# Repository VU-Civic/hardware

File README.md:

# CivicAlert Hardware Design Repository

This repository contains hardware design files for the CivicAlert sensor device. The design was created
using [KiCad](https://www.kicad.org/download) and requires v9.0.0 or later to open and edit.

The CivicAlert gunshot sensor is a self-contained PCB which utilizes four audio channels, a digital
compass and IMU, GNSS satellite data, and a state-of-the-art AI-based classification model to detect
gunshots in its vicinity. Relevant event information and evidential audio clips can be transferred to
a cloud server for futher processing using a dedicated cellular-based Internet of Things (IoT) network.

## Getting Started

1. Clone this repo on your local machine
2. Download and install [KiCad](https://www.kicad.org/download)
3. Open KiCad
4. Click `File->Open Project`
5. Select `hw.kicad_pro` from the repo root directory

You will be presented with a listing of available KiCad tools for this project. The two most relevant are
the "Schematic Editor" and the "PCB Editor". The Schematic Editor allows you to view and manipulate the
logical connections between hardware components and power networks, while the "PCB Editor" allows you to
view the actual design of the board and layout of the components as they will be placed during
manufacturing and assembly.

The schematic symbols and footprints for all parts and components used in this design have been stored
within the repo itself and should automatically be picked up by KiCad when you open the project. If you
would like to add new parts or alter existing ones, you may use the "Symbol Editor" or "Footprint
Editor" tool, and ensure that any new parts are stored in either `part_symbols/` or `part_footprints/`
so that new parts will be visible and available to others in the future.

Additionally, 3D CAD models for all parts can be found in `part_3d_cads/`, which will be used by KiCad
to generate a 3D rendering of the final assembled board. Finally, all datasheets, application notes,
and relevant part-specific documentation can be in the `datasheets/` folder.

## Revisions

### Revision A
*Release Date: 03-13-2025*

Original prototype version of the hardware. Expected usage includes:

* 4 audio channels to allow computation of 3D angles of arrival
* Digital compass + IMU to align angles of arrival with a global coordinate system
* Multi-constellation GNSS receiver to ensure accurate timestamping in difficult environments
* Micro-SIM card to provide direct connectivity to Thingstream for cellular data offloading
* Event detection and angle of arrival calculations performed on primary MCU
* Event classification and validation performed using AI models on external Raspberry Pi
* Data communication between primary MCU and Raspberry Pi uses USB over internal connector
* Data communication between primary MCU and external debugging machine (PC) uses USB-C connector
* Internal switch automatically routes primary MCU output to correct USB interface depending on the
  presence or absence of a connected Raspberry Pi Compute Module
* Entire board (including Raspberry Pi) is powered from a 5V USB-C cable
* Firmware flashing requires an open-ended card edge connector from
  [Kyocera AVX](https://www.digikey.com/en/products/detail/kyocera-avx/009159010061911/11307835)
  and an STLink-V3MINIE programmer from
  [STMicroelectronics](https://www.digikey.com/en/products/detail/stmicroelectronics/STLINK-V3MINIE/16284301)

Major functionality and components are shown below:

### Revision B
*Release Date: 08-01-2025*

Updated to support edge-based AI and remove the need for an external Raspberry Pi Compute Module:

TODO: Board Designs

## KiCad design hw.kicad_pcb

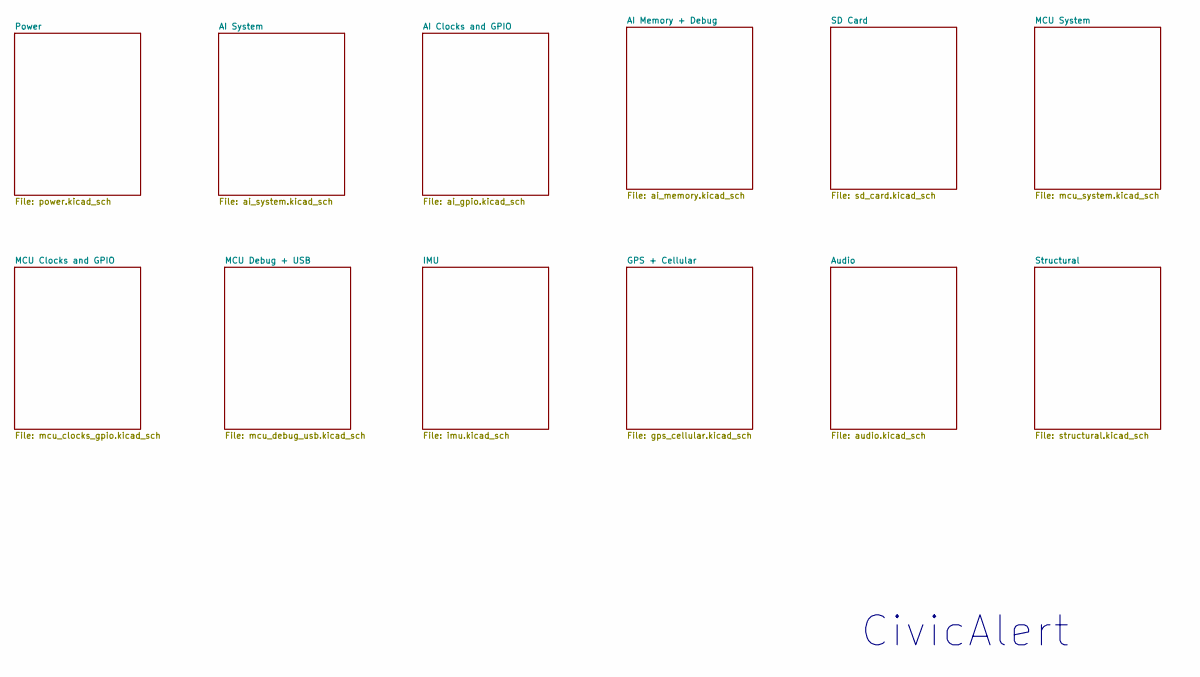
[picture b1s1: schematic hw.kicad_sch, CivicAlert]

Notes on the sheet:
CivicAlert

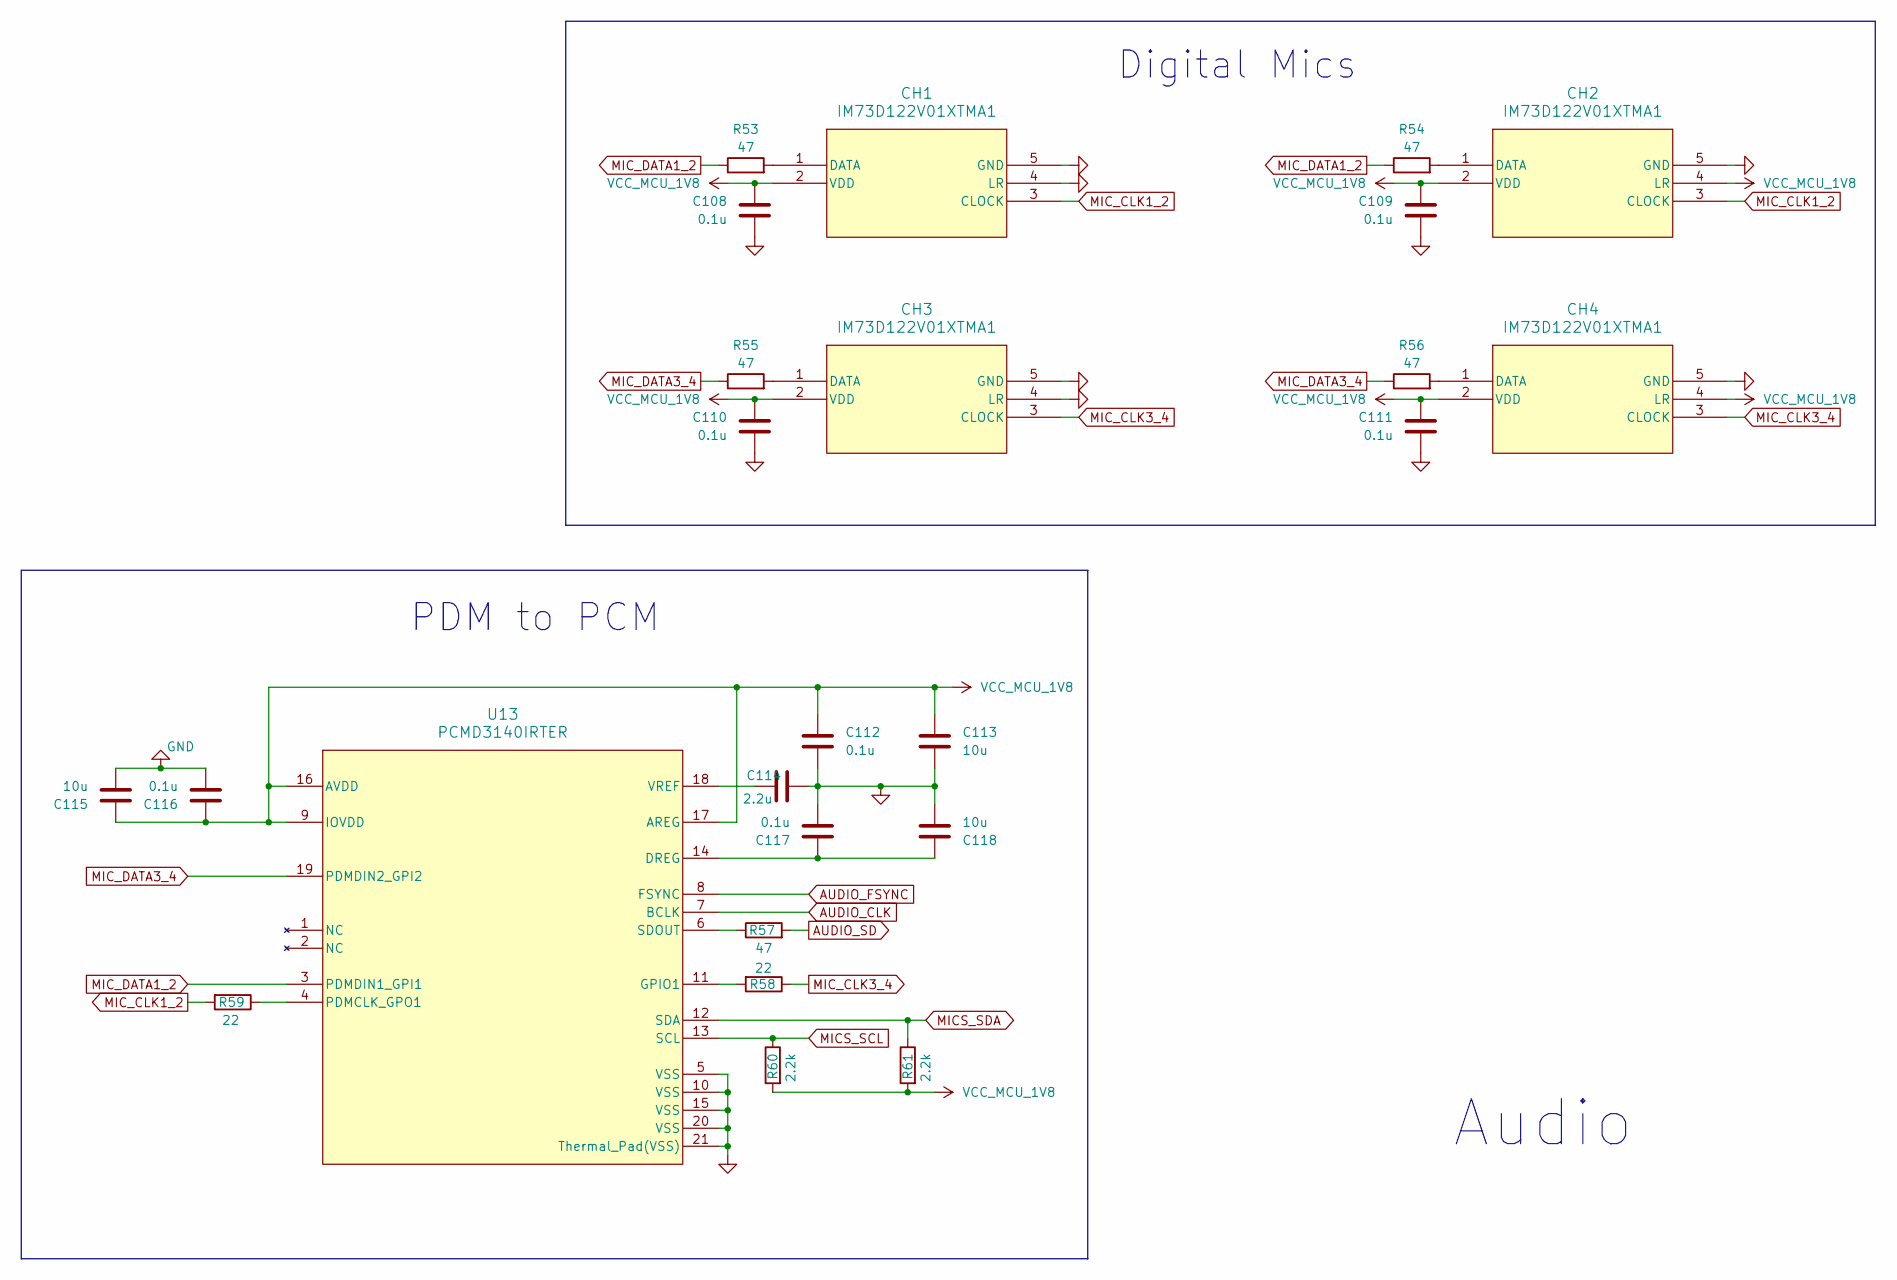
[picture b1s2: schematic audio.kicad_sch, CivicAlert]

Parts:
C108, C109, C110, C111, C112, C116, C117: 0.1u; C_0402_1005Metric; MPN GRM155R71C104KA88J
C113, C115, C118: 10u; C_0603_1608Metric; MPN GRM188Z71A106KA73D
C114: 2.2u; C_0402_1005Metric; MPN GRT155C71A225KE13D
CH1, CH2, CH3, CH4: IM73D122V01XTMA1; MPN IM73D122V01XTMA1
R53, R54, R55, R56, R57: 47; R_0402_1005Metric
R58, R59: 22; R_0402_1005Metric
R60, R61: 2.2k; R_0402_1005Metric
U13: PCMD3140IRTER; MPN PCMD3140IRTER

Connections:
AUDIO_CLK: U13.7 (BCLK); also elsewhere on the board
AUDIO_FSYNC: U13.8 (FSYNC); also elsewhere on the board
AUDIO_SD: R57.2; also elsewhere on the board
GND: C108.2, C109.2, C110.2, C111.2, C112.2, C113.2, C114.2, C115.2, C116.2, C117.2, C118.2, CH1.4 (LR), CH1.5 (GND), CH2.5 (GND), CH3.4 (LR), CH3.5 (GND), CH4.5 (GND), U13.5 (VSS), U13.10 (VSS), U13.15 (VSS), U13.20 (VSS), U13.21 (Thermal_Pad(VSS)); also elsewhere on the board
MICS_SCL: R60.1, U13.13 (SCL); also elsewhere on the board
MICS_SDA: R61.1, U13.12 (SDA); also elsewhere on the board
MIC_CLK1_2: CH1.3 (CLOCK), CH2.3 (CLOCK), R59.2
MIC_CLK3_4: CH3.3 (CLOCK), CH4.3 (CLOCK), R58.1
MIC_DATA1_2: R53.1, R54.1, U13.3 (PDMDIN1_GPI1)
MIC_DATA3_4: R55.1, R56.1, U13.19 (PDMDIN2_GPI2)
unnamed: CH1.1 (DATA), R53.2
unnamed: CH2.1 (DATA), R54.2
unnamed: CH3.1 (DATA), R55.2
unnamed: CH4.1 (DATA), R56.2
unnamed: C117.1, C118.1, U13.14 (DREG)
unnamed: R58.2, U13.11 (GPIO1)
unnamed: R59.1, U13.4 (PDMCLK_GPO1)
unnamed: R57.1, U13.6 (SDOUT)
unnamed: C114.1, U13.18 (VREF)
VCC_MCU_1V8: C108.1, C109.1, C110.1, C111.1, C112.1, C113.1, C115.1, C116.1, CH1.2 (VDD), CH2.2 (VDD), CH2.4 (LR), CH3.2 (VDD), CH4.2 (VDD), CH4.4 (LR), R60.2, R61.2, U13.9 (IOVDD), U13.16 (AVDD), U13.17 (AREG); also elsewhere on the board

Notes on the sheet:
Digital Mics
PDM to PCM
Audio

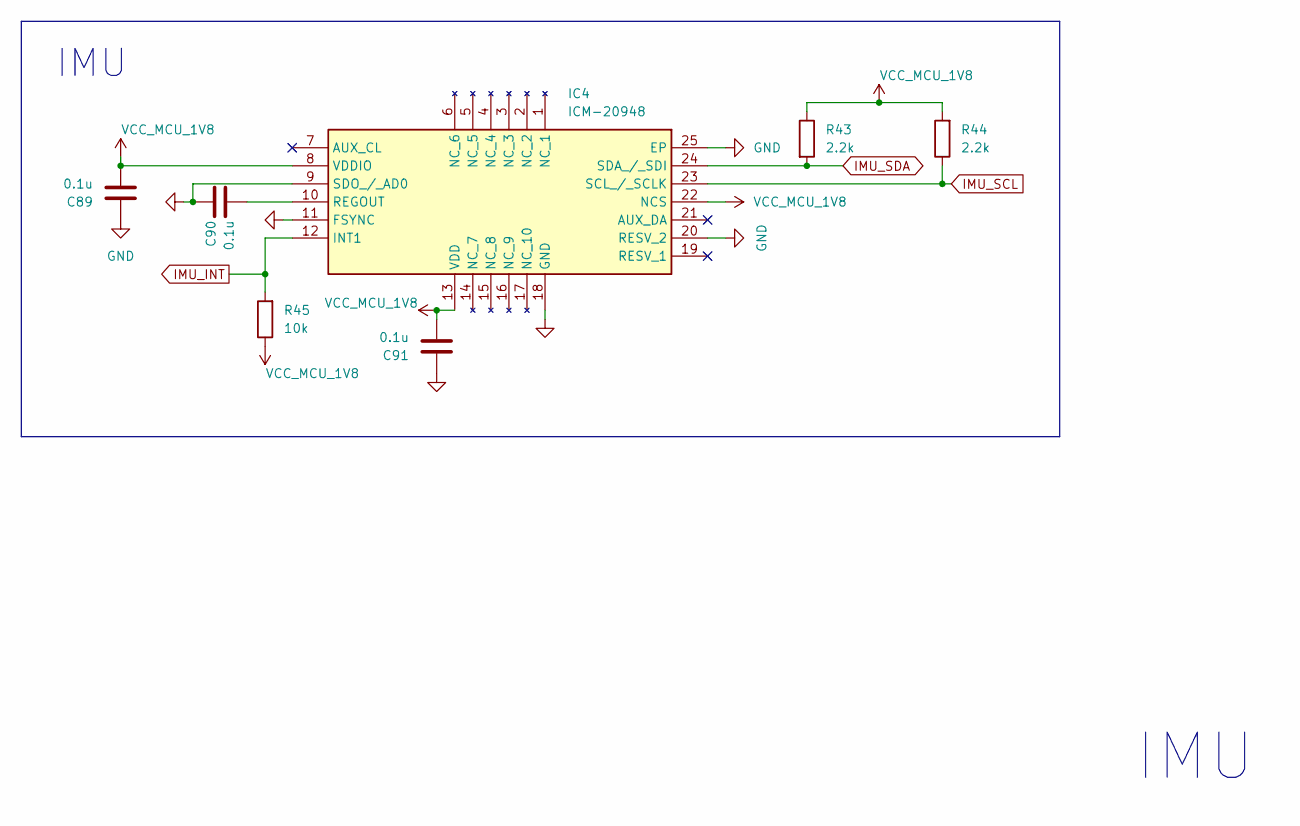
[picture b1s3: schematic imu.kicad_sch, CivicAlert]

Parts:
C89, C90, C91: 0.1u; C_0402_1005Metric; MPN GRM155R71C104KA88J
IC4: ICM-20948; MPN ICM-20948
R43, R44: 2.2k; R_0402_1005Metric
R45: 10k; R_0402_1005Metric

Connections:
GND: C89.1, C90.1, C91.1, IC4.9 (SDO_/_AD0), IC4.11 (FSYNC), IC4.18 (GND), IC4.20 (RESV_2), IC4.25 (EP); also elsewhere on the board
IMU_INT: IC4.12 (INT1), R45.2; also elsewhere on the board
IMU_SCL: IC4.23 (SCL_/_SCLK), R44.1; also elsewhere on the board
IMU_SDA: IC4.24 (SDA_/_SDI), R43.2; also elsewhere on the board
unnamed: C90.2, IC4.10 (REGOUT)
VCC_MCU_1V8: C89.2, C91.2, IC4.8 (VDDIO), IC4.13 (VDD), IC4.22 (NCS), R43.1, R44.2, R45.1; also elsewhere on the board

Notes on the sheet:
IMU

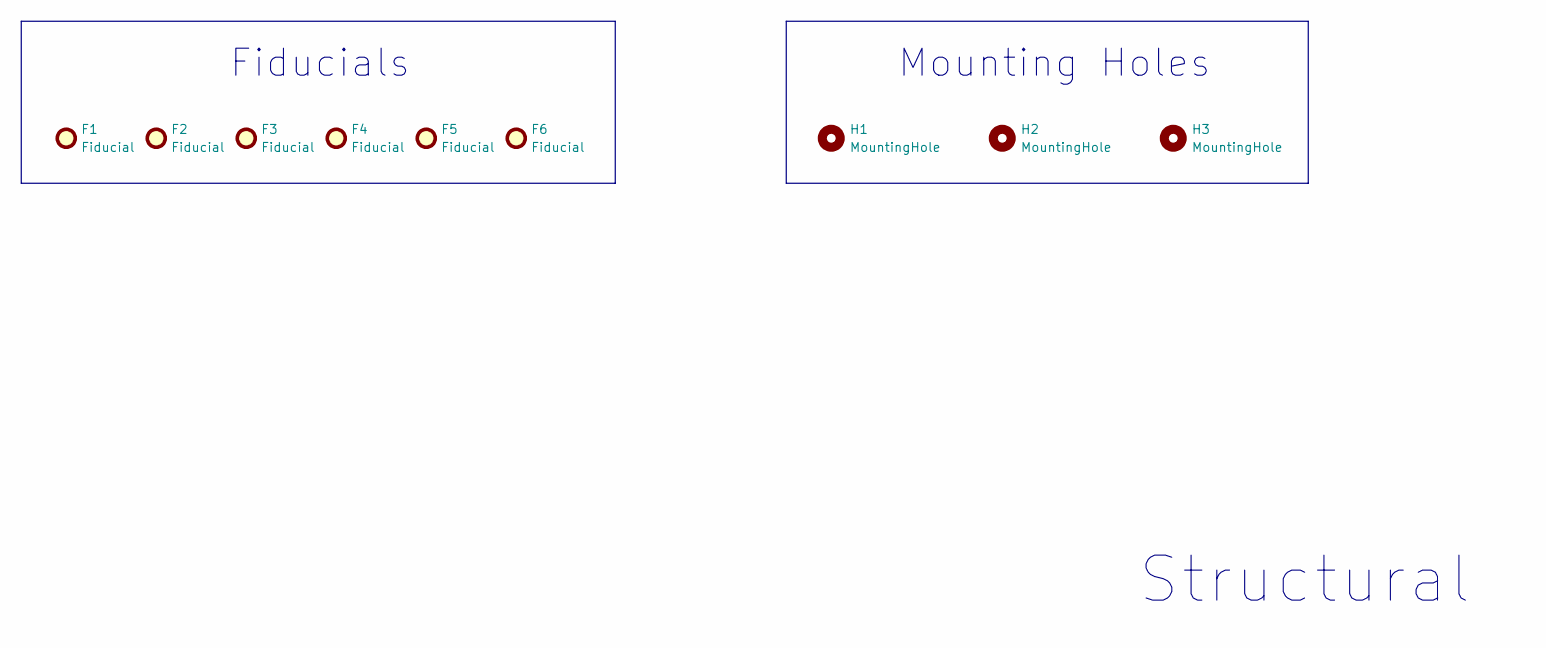
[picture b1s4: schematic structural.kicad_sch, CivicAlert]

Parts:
F1, F2, F3, F4, F5, F6: Fiducial; Fiducial_1mm_Mask3mm
H1, H2, H3: MountingHole; MountingHole_2.2mm_M2

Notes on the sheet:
Structural
Mounting Holes
Fiducials

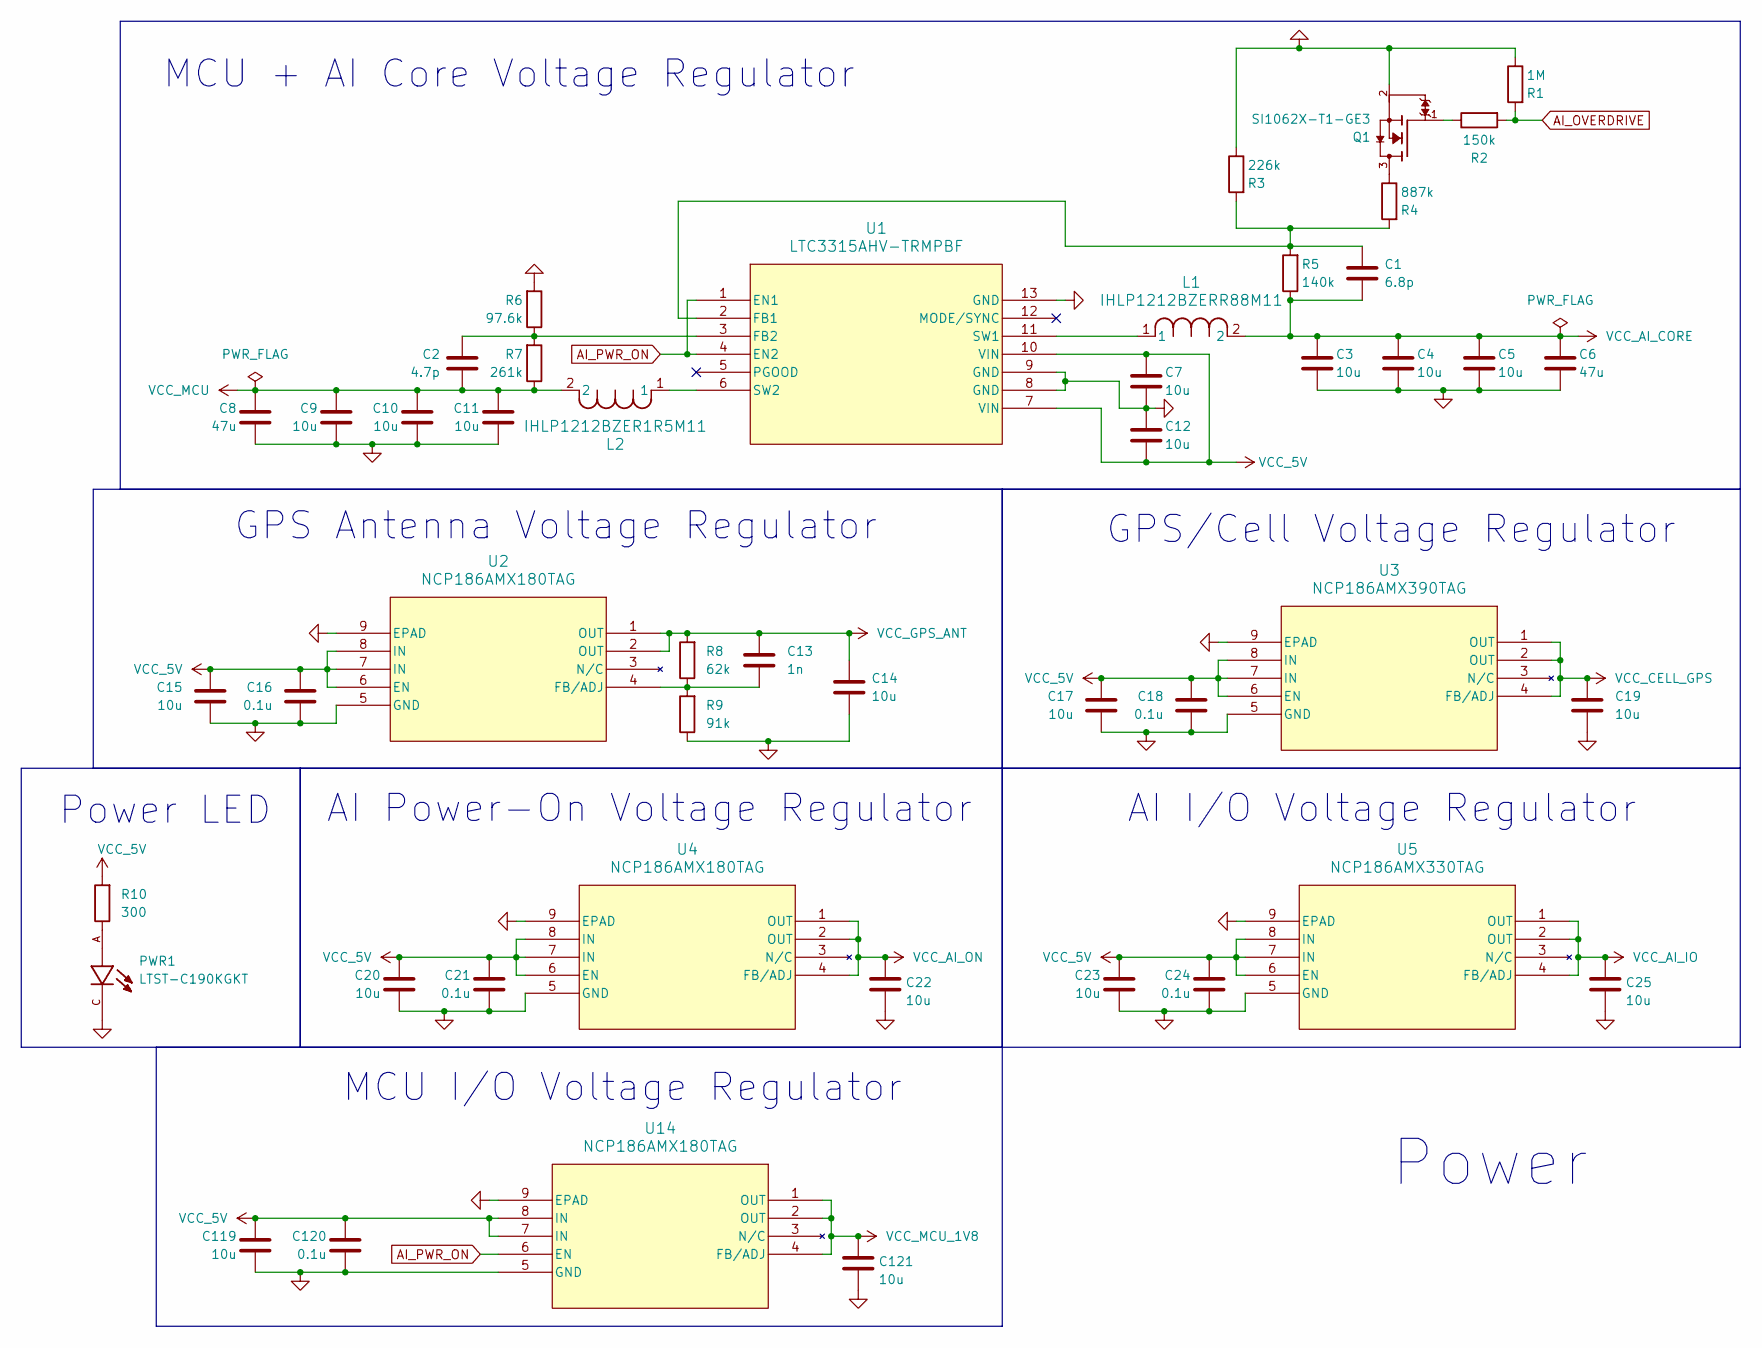
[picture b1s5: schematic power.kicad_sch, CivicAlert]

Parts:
C1: 6.8p; C_0402_1005Metric; MPN GCM1555C1H6R8BA16J
C2: 4.7p; C_0402_1005Metric; MPN GCM1555C1H4R7CA16D
C3, C4, C5, C7, C9, C10, C11, C12: 10u; C_0805_2012Metric; MPN CGA4J1X7R0J106M125AC
C6, C8: 47u; C_1206_3216Metric; MPN C3216X7S0J476M160AC
C13: 1n; C_0402_1005Metric; MPN GRM155R71H102JA01J
C14, C15, C17, C19, C20, C22, C23, C25, C119, C121: 10u; C_0603_1608Metric; MPN GRM188Z71A106KA73D
C16, C18, C21, C24, C120: 0.1u; C_0402_1005Metric; MPN GRM155R71C104KA88J
L1: IHLP1212BZERR88M11; MPN IHLP1212BZERR88M11
L2: IHLP1212BZER1R5M11; MPN IHLP1212BZER1R5M11
PWR1: LTST-C190KGKT; MPN LTST-C190KGKT
Q1: SI1062X-T1-GE3; MPN SI1062X-T1-GE3
R1: 1M; R_0402_1005Metric
R2: 150k; R_0402_1005Metric
R3: 226k; R_0603_1608Metric; MPN RT0603BRD07226KL
R4: 887k; R_0603_1608Metric; MPN RT0603BRD07887KL
R5: 140k; R_0603_1608Metric; MPN RT0603BRD07140KL
R6: 97.6k; R_0603_1608Metric; MPN RT0603BRD0797K6L
R7: 261k; R_0603_1608Metric; MPN RT0603BRD07261KL
R8: 62k; R_0402_1005Metric
R9: 91k; R_0402_1005Metric
R10: 300; R_0402_1005Metric
U1: LTC3315AHV-TRMPBF; LTC3315AHV; MPN LTC3315AHV-TRMPBF
U2, U4, U14: NCP186AMX180TAG; NCP186AMX; MPN NCP186AMX180TAG
U3: NCP186AMX390TAG; NCP186AMX; MPN NCP186AMX390TAG
U5: NCP186AMX330TAG; NCP186AMX; MPN NCP186AMX330TAG

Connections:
AI_OVERDRIVE: R1.2, R2.2; also elsewhere on the board
AI_PWR_ON: U1.1 (EN1), U1.4 (EN2), U14.6 (EN); also elsewhere on the board
GND: C3.2, C4.2, C5.2, C6.2, C7.2, C8.2, C9.2, C10.2, C11.2, C12.1, C14.2, C15.2, C16.2, C17.2, C18.2, C19.2, C20.2, C21.2, C22.2, C23.2, C24.2, C25.2, C119.2, C120.2, C121.2, PWR1.C, Q1.2, R1.1, R3.1, R6.2, R9.1, U1.8 (GND), U1.9 (GND), U1.13 (GND), U2.5 (GND), U2.9 (EPAD), U3.5 (GND), U3.9 (EPAD), U4.5 (GND), U4.9 (EPAD), U5.5 (GND), U5.9 (EPAD), U14.5 (GND), U14.9 (EPAD); also elsewhere on the board
unnamed: PWR1.A, R10.1
unnamed: Q1.1, R2.1
unnamed: Q1.3, R4.1
unnamed: C1.1, R3.2, R4.2, R5.2, U1.2 (FB1)
unnamed: C2.1, R6.1, R7.2, U1.3 (FB2)
unnamed: L1.1, U1.11 (SW1)
unnamed: L2.1, U1.6 (SW2)
unnamed: C13.2, R8.1, R9.2, U2.4 (FB/ADJ)
VCC_5V: C7.1, C12.2, C15.1, C16.1, C17.1, C18.1, C20.1, C21.1, C23.1, C24.1, C119.1, C120.1, R10.2, U1.7 (VIN), U1.10 (VIN), U2.6 (EN), U2.7 (IN), U2.8 (IN), U3.6 (EN), U3.7 (IN), U3.8 (IN), U4.6 (EN), U4.7 (IN), U4.8 (IN), U5.6 (EN), U5.7 (IN), U5.8 (IN), U14.7 (IN), U14.8 (IN); also elsewhere on the board
VCC_AI_CORE: C1.2, C3.1, C4.1, C5.1, C6.1, L1.2, R5.1; also elsewhere on the board
VCC_AI_IO: C25.1, U5.1 (OUT), U5.2 (OUT), U5.4 (FB/ADJ); also elsewhere on the board
VCC_AI_ON: C22.1, U4.1 (OUT), U4.2 (OUT), U4.4 (FB/ADJ); also elsewhere on the board
VCC_CELL_GPS: C19.1, U3.1 (OUT), U3.2 (OUT), U3.4 (FB/ADJ); also elsewhere on the board
VCC_GPS_ANT: C13.1, C14.1, R8.2, U2.1 (OUT), U2.2 (OUT); also elsewhere on the board
VCC_MCU: C2.2, C8.1, C9.1, C10.1, C11.1, L2.2, R7.1; also elsewhere on the board
VCC_MCU_1V8: C121.1, U14.1 (OUT), U14.2 (OUT), U14.4 (FB/ADJ); also elsewhere on the board

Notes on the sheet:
GPS/Cell Voltage Regulator
AI I/O Voltage Regulator
Power LED
MCU + AI Core Voltage Regulator
GPS Antenna Voltage Regulator
AI Power-On Voltage Regulator
MCU I/O Voltage Regulator
Power

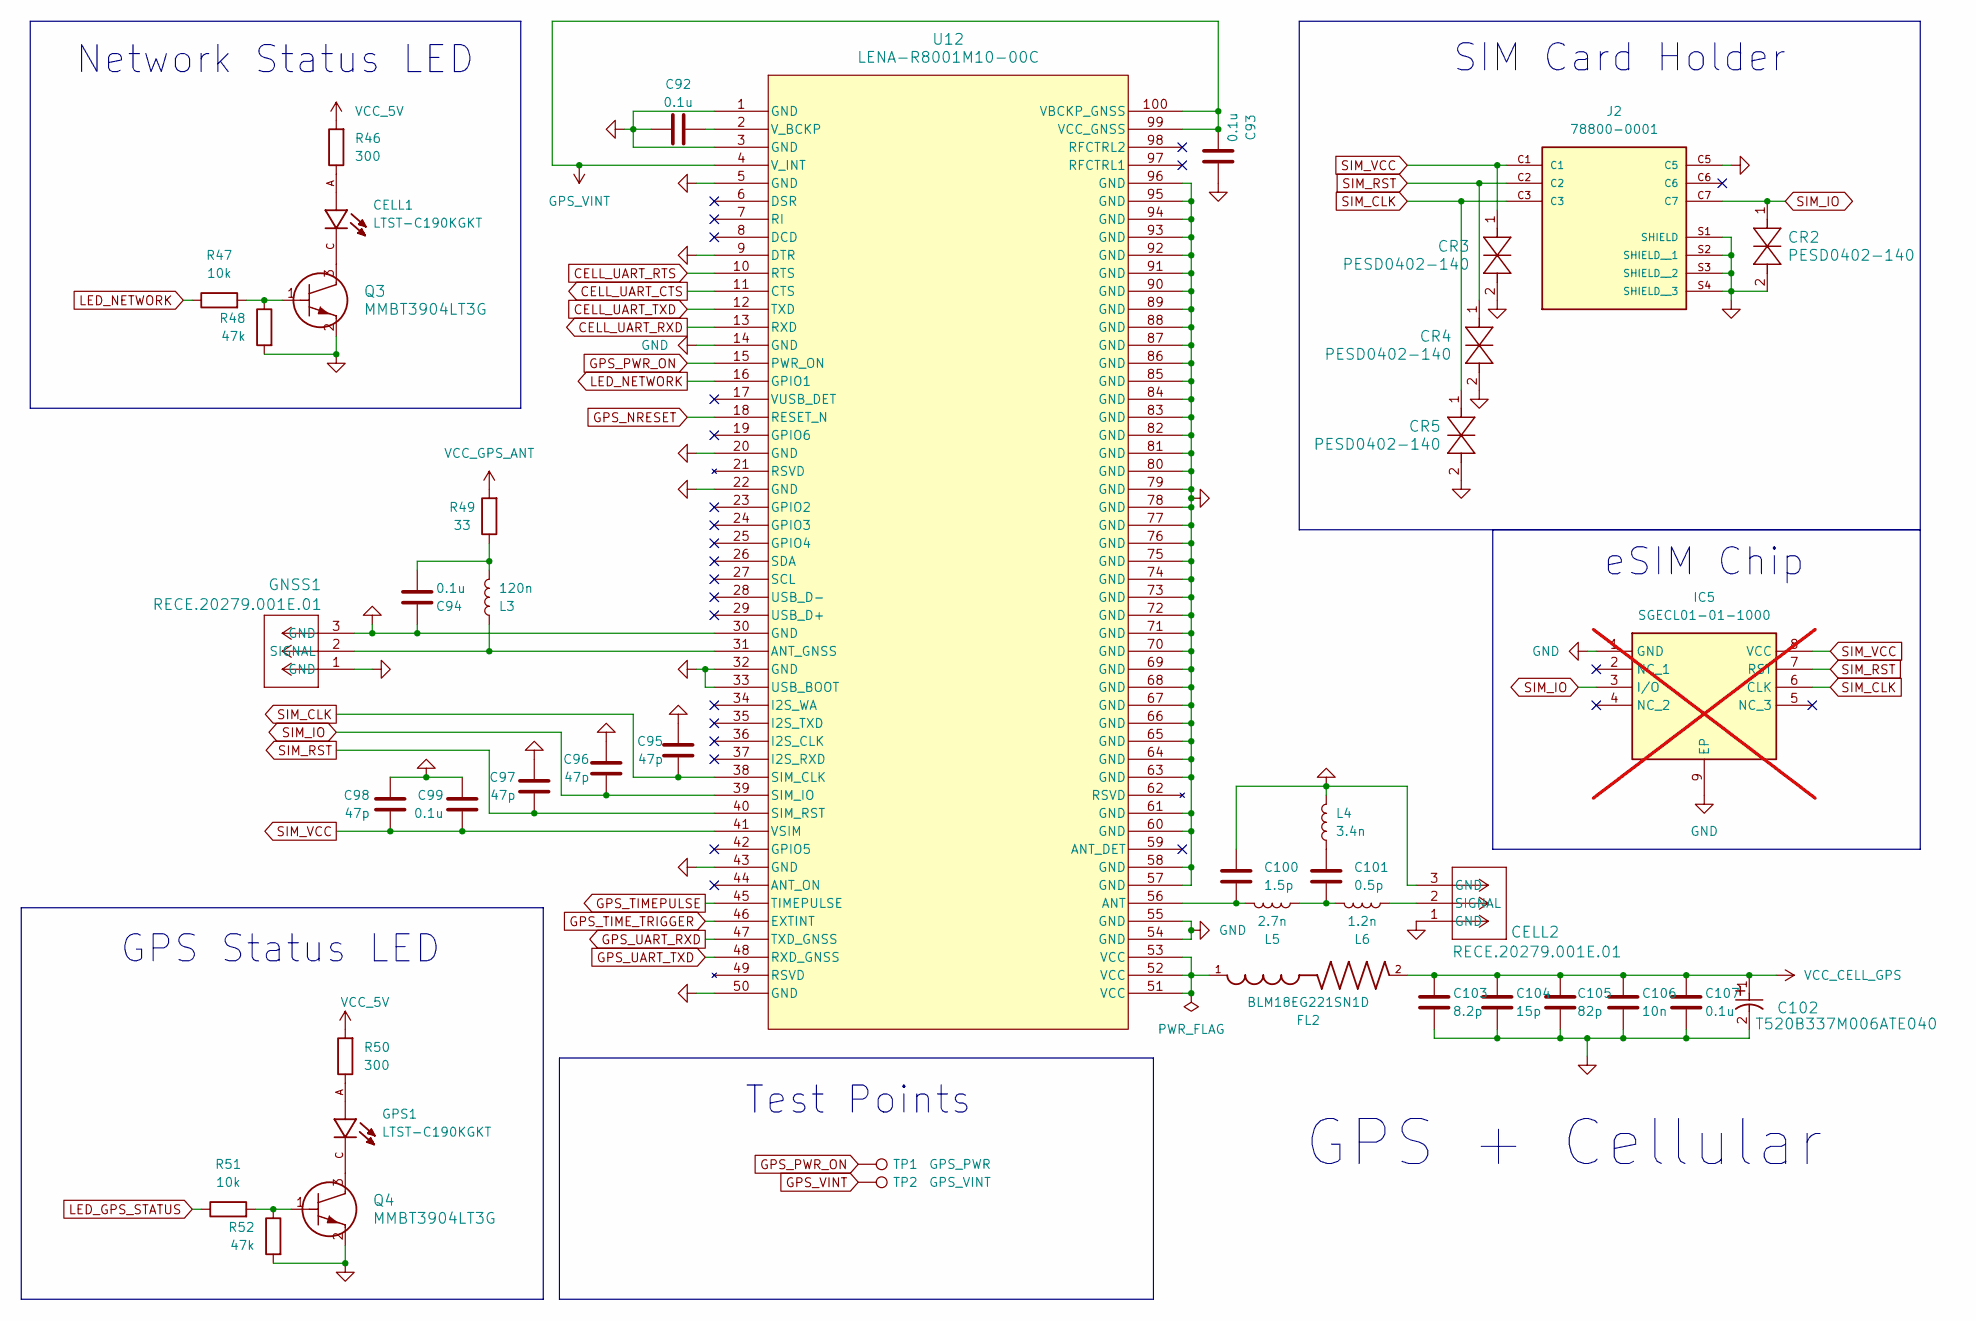
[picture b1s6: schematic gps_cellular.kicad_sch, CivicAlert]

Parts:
C92, C93, C94, C99, C107: 0.1u; C_0402_1005Metric; MPN GRM155R71C104KA88J
C95, C96, C97, C98: 47p; C_0402_1005Metric; MPN GRT1555C1H470JA02J
C100: 1.5p; C_0402_1005Metric; MPN GRT1555C1H1R5CA02J
C101: 0.5p; C_0402_1005Metric; MPN GJM1555C1HR50WB01D
C102: T520B337M006ATE040; MPN T520B337M006ATE040
C103: 8.2p; C_0402_1005Metric; MPN GRM1555C1E8R2CA01D
C104: 15p; C_0402_1005Metric; MPN GRT1555C1H150JA02J
C105: 82p; C_0402_1005Metric; MPN GRT1555C1H820FA02D
C106: 10n; C_0402_1005Metric; MPN GCM155R71H103KA55D
CELL1: LTST-C190KGKT; MPN LTST-C190KGKT
CELL2: RECE.20279.001E.01; MPN RECE.20279.001E.01
CR2, CR3, CR4, CR5: PESD0402-140; PESD0402-140_LTF; MPN PESD0402-140
FL2: BLM18EG221SN1D; MPN BLM18EG221SN1D
GNSS1: RECE.20279.001E.01; MPN RECE.20279.001E.01
GPS1: LTST-C190KGKT; MPN LTST-C190KGKT
IC5: SGECL01-01-1000; not fitted
J2: 78800-0001; 0788000001; MPN 0788000001
L3: 120n; L_0402_1005Metric; MPN LQW15ANR12J00
L4: 3.4n; L_0402_1005Metric; MPN LQG15WZ3N4S02D
L5: 2.7n; L_0402_1005Metric; MPN LQG15HS2N7B02D
L6: 1.2n; L_0402_1005Metric; MPN LQG15HS1N2B02D
Q3, Q4: MMBT3904LT3G; MPN BC847CE6327HTSA1
R46, R50: 300; R_0402_1005Metric
R47, R51: 10k; R_0402_1005Metric
R48, R52: 47k; R_0402_1005Metric
R49: 33; R_0402_1005Metric
TP1: GPS_PWR; TestPoint_THTPad_D1.0mm_Drill0.5mm
TP2: GPS_VINT; TestPoint_THTPad_D1.0mm_Drill0.5mm
U12: LENA-R8001M10-00C; MPN LENA-R8001M10-00C

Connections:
CELL_UART_CTS: U12.11 (CTS); also elsewhere on the board
CELL_UART_RTS: U12.10 (RTS); also elsewhere on the board
CELL_UART_RXD: U12.13 (RXD); also elsewhere on the board
CELL_UART_TXD: U12.12 (TXD); also elsewhere on the board
GND: C92.2, C93.2, C94.1, C95.1, C96.1, C97.1, C98.1, C99.1, C100.1, C102.2, C103.2, C104.2, C105.2, C106.2, C107.2, CELL2.1 (GND), CELL2.3 (GND), CR2.2, CR3.2, CR4.2, CR5.2, GNSS1.1 (GND), GNSS1.3 (GND), IC5.1 (GND), IC5.9 (EP), J2.C5, J2.S1 (SHIELD), J2.S2 (SHIELD__1), J2.S3 (SHIELD__2), J2.S4 (SHIELD__3), L4.2, Q3.2, Q4.2, R48.2, R52.2, U12.1 (GND), U12.3 (GND), U12.5 (GND), U12.9 (DTR), U12.14 (GND), U12.20 (GND), U12.22 (GND), U12.30 (GND), U12.32 (GND), U12.33 (USB_BOOT), U12.43 (GND), U12.50 (GND), U12.54 (GND), U12.55 (GND), U12.57 (GND), U12.58 (GND), U12.60 (GND), U12.61 (GND), U12.63 (GND), U12.64 (GND), U12.65 (GND), U12.66 (GND), U12.67 (GND), U12.68 (GND), U12.69 (GND), U12.70 (GND), U12.71 (GND), U12.72 (GND), U12.73 (GND), U12.74 (GND), U12.75 (GND), U12.76 (GND), U12.77 (GND), U12.78 (GND), U12.79 (GND), U12.80 (GND), U12.81 (GND), U12.82 (GND), U12.83 (GND), U12.84 (GND), U12.85 (GND), U12.86 (GND), U12.87 (GND), U12.88 (GND), U12.89 (GND), U12.90 (GND), U12.91 (GND), U12.92 (GND), U12.93 (GND), U12.94 (GND), U12.95 (GND), U12.96 (GND); also elsewhere on the board
GPS_NRESET: U12.18 (RESET_N); also elsewhere on the board
GPS_PWR_ON: TP1.1, U12.15 (PWR_ON); also elsewhere on the board
GPS_TIMEPULSE: U12.45 (TIMEPULSE); also elsewhere on the board
GPS_TIME_TRIGGER: U12.46 (EXTINT); also elsewhere on the board
GPS_UART_RXD: U12.47 (TXD_GNSS); also elsewhere on the board
GPS_UART_TXD: U12.48 (RXD_GNSS); also elsewhere on the board
GPS_VINT: C93.1, TP2.1, U12.4 (V_INT), U12.99 (VCC_GNSS), U12.100 (VBCKP_GNSS)
LED_GPS_STATUS: R51.1; also elsewhere on the board
LED_NETWORK: R47.1, U12.16 (GPIO1)
unnamed: C94.2, L3.2, R49.1
unnamed: C101.1, L4.1
unnamed: C101.2, L5.2, L6.1
unnamed: CELL1.A, R46.1
unnamed: CELL1.C, Q3.3
unnamed: CELL2.2 (SIGNAL), L6.2
unnamed: FL2.1, U12.51 (VCC), U12.52 (VCC), U12.53 (VCC)
unnamed: GNSS1.2 (SIGNAL), L3.1, U12.31 (ANT_GNSS)
unnamed: GPS1.A, R50.1
unnamed: GPS1.C, Q4.3
unnamed: Q3.1, R47.2, R48.1
unnamed: Q4.1, R51.2, R52.1
unnamed: C100.2, L5.1, U12.56 (ANT)
unnamed: C92.1, U12.2 (V_BCKP)
SIM_CLK: C95.2, CR5.1, IC5.6 (CLK), J2.C3, U12.38 (SIM_CLK)
SIM_IO: C96.2, CR2.1, IC5.3 (I/O), J2.C7, U12.39 (SIM_IO)
SIM_RST: C97.2, CR4.1, IC5.7 (RST), J2.C2, U12.40 (SIM_RST)
SIM_VCC: C98.2, C99.2, CR3.1, IC5.8 (VCC), J2.C1, U12.41 (VSIM)
VCC_5V: R46.2, R50.2; also elsewhere on the board
VCC_CELL_GPS: C102.1, C103.1, C104.1, C105.1, C106.1, C107.1, FL2.2; also elsewhere on the board
VCC_GPS_ANT: R49.2; also elsewhere on the board

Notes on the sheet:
GPS Status LED
Test Points
Network Status LED
GPS + Cellular
SIM Card Holder
eSIM Chip

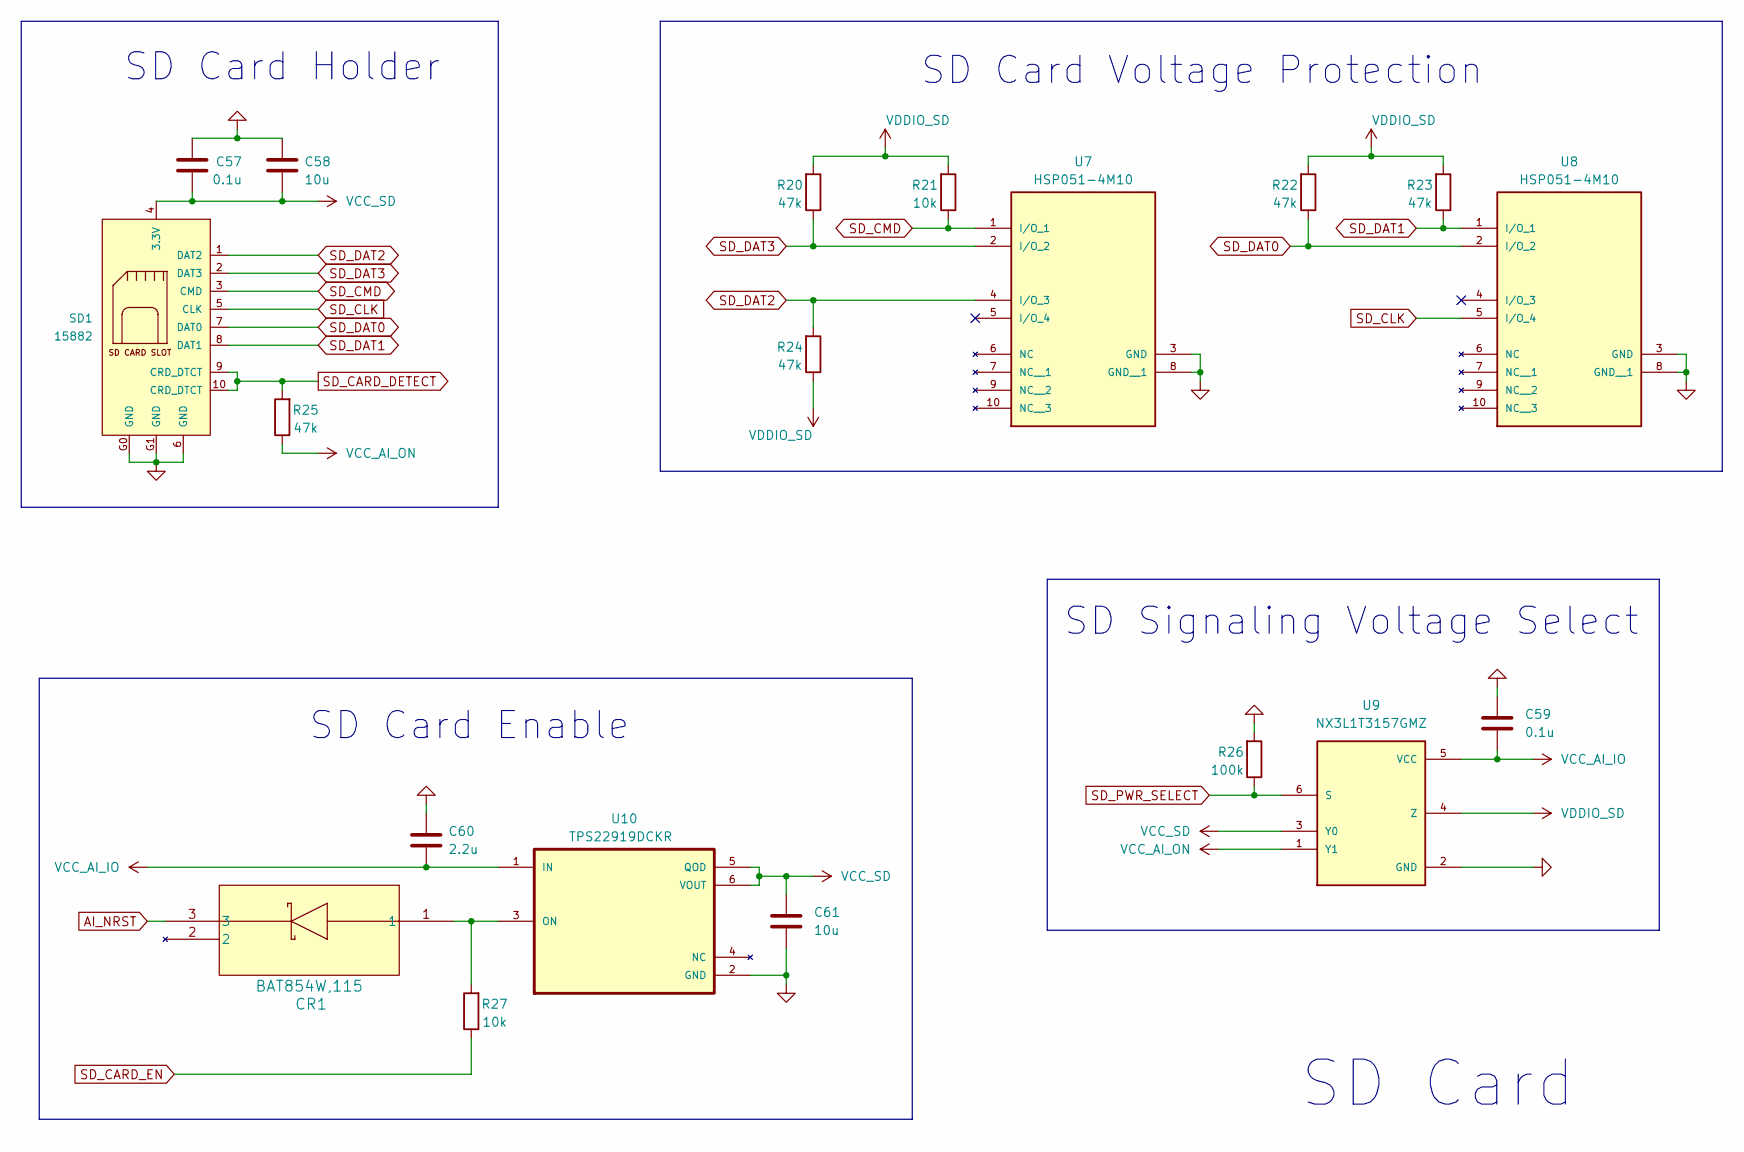
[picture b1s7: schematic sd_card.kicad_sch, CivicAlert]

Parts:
C57, C59: 0.1u; C_0402_1005Metric; MPN GRM155R71C104KA88J
C58, C61: 10u; C_0603_1608Metric; MPN GRM188Z71A106KA73D
C60: 2.2u; C_0402_1005Metric; MPN GRT155C71A225KE13D
CR1: BAT854W,115; BAT854AW,115; MPN BAT854W,115
R20, R22, R23, R24, R25: 47k; R_0402_1005Metric
R21, R27: 10k; R_0402_1005Metric
R26: 100k; R_0402_1005Metric
SD1: 15882; MPN 15882
U7, U8: HSP051-4M10; MPN HSP051-4M10
U9: NX3L1T3157GMZ; MPN NX3L1T3157GMZ
U10: TPS22919DCKR; MPN TPS22919DCKR

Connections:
AI_NRST: CR1.3; also elsewhere on the board
GND: C57.1, C58.1, C59.1, C60.1, C61.2, R26.2, SD1.6 (GND), SD1.G0 (GND), SD1.G1 (GND), U7.3 (GND), U7.8 (GND__1), U8.3 (GND), U8.8 (GND__1), U9.2 (GND), U10.2 (GND); also elsewhere on the board
unnamed: CR1.1, R27.2, U10.3 (ON)
SD_CARD_DETECT: R25.2, SD1.9 (CRD_DTCT), SD1.10 (CRD_DTCT); also elsewhere on the board
SD_CARD_EN: R27.1; also elsewhere on the board
SD_CLK: SD1.5 (CLK), U8.5 (I/O_4); also elsewhere on the board
SD_CMD: R21.1, SD1.3 (CMD), U7.1 (I/O_1); also elsewhere on the board
SD_DAT0: R22.1, SD1.7 (DAT0), U8.2 (I/O_2); also elsewhere on the board
SD_DAT1: R23.1, SD1.8 (DAT1), U8.1 (I/O_1); also elsewhere on the board
SD_DAT2: R24.2, SD1.1 (DAT2), U7.4 (I/O_3); also elsewhere on the board
SD_DAT3: R20.1, SD1.2 (DAT3), U7.2 (I/O_2); also elsewhere on the board
SD_PWR_SELECT: R26.1, U9.6 (S); also elsewhere on the board
VCC_AI_IO: C59.2, C60.2, U9.5 (VCC), U10.1 (IN); also elsewhere on the board
VCC_AI_ON: R25.1, U9.1 (Y1); also elsewhere on the board
VCC_SD: C57.2, C58.2, C61.1, SD1.4 (3.3V), U9.3 (Y0), U10.5 (QOD), U10.6 (VOUT)
VDDIO_SD: R20.2, R21.2, R22.2, R23.2, R24.1, U9.4 (Z); also elsewhere on the board

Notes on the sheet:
SD Card Voltage Protection
SD Card
SD Card Enable
SD Signaling Voltage Select
SD Card Holder
